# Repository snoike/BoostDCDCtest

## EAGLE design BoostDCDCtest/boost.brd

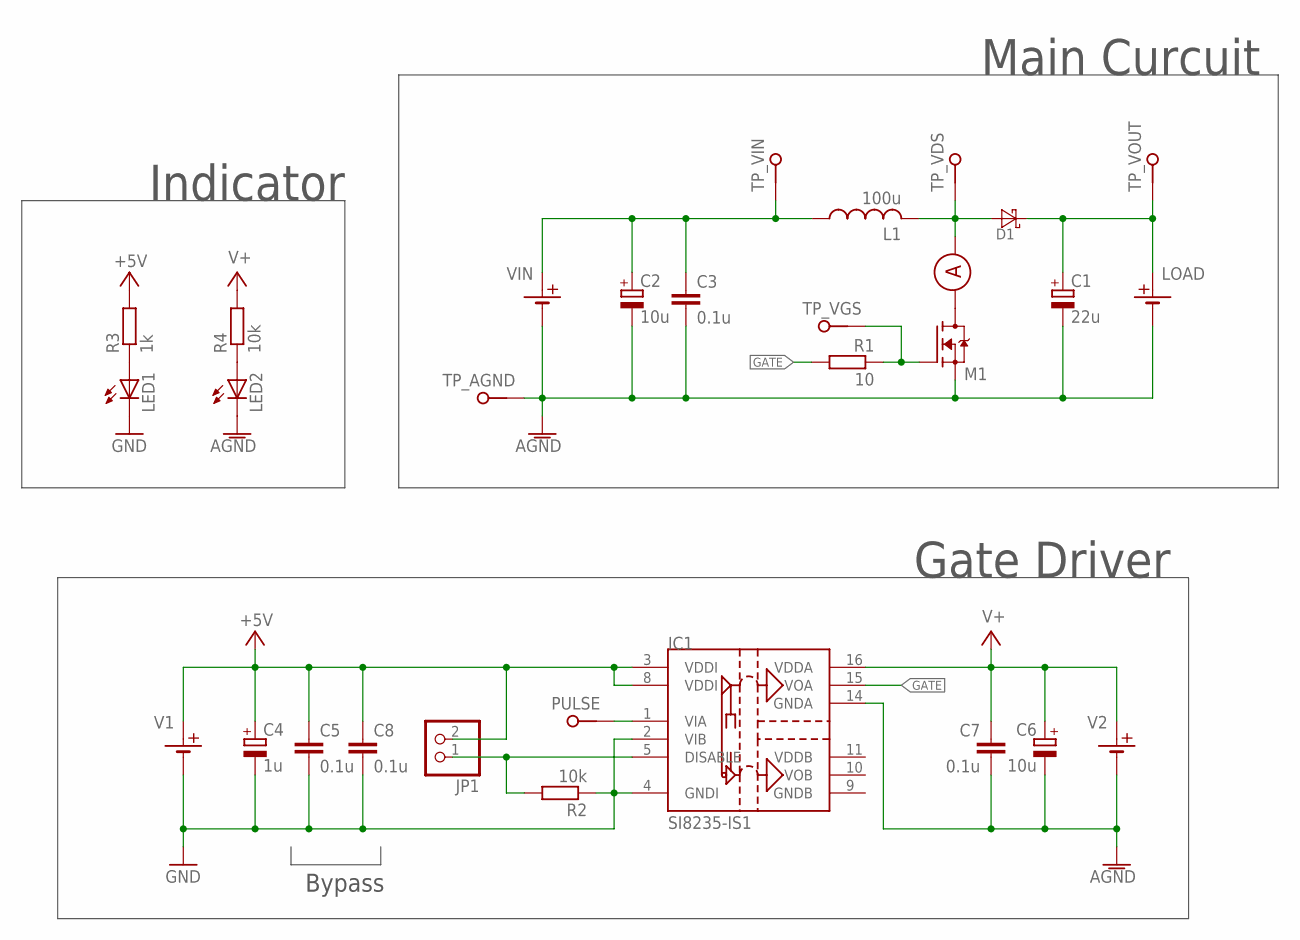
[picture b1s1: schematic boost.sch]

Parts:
C1: 22u; E5-10,5
C2, C6: 10u; E2,5-6
C3, C5, C7, C8: 0.1u; C0805
C4: 1u; E2-5
D1: RB088LAM150TFTR; SOD128
IC1: SI8235-IS1; SO16
JP1: PINHD-1X2; 1X02
L1: 100u; MURATA_19RXXXC
LED1, LED2: LEDCHIPLED_0805; CHIPLED_0805
LOAD: POWER_SUPPLY_L; SOURCE_HIGH
M1: FET_ON_SOCKET; ICTS-TO3P
PULSE: PIN
R1: 10; R2512
R2, R4: 10k; R0805
R3: 1k; R0805
TP_AGND: PIN
TP_VDS: PIN
TP_VGS: PIN
TP_VIN: PIN
TP_VOUT: PIN
U$1: AMMETER
V1, V2: POWER_SUPPLY; 526702AX
VIN: POWER_SUPPLY_L; SOURCE_HIGH

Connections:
+5V: C4.+, C5.1, C8.1, IC1.3 (VDDI), IC1.8 (VDDI), JP1.2, R3.2, V1.P
AGND: C1.-, C2.-, C3.2, C6.-, C7.2, IC1.14 (GNDA), LED2.C, LOAD.N, M1.S0 (S), M1.S1 (S), TP_AGND.1, V2.N, VIN.N
GATE: IC1.15 (VOA), R1.2
GND: C4.-, C5.2, C8.2, IC1.2 (VIB), IC1.4 (GNDI), LED1.C, R2.1, V1.N
GNDB: IC1.9 (GNDB)
unnamed: C2.+, C3.1, L1.1, TP_VIN.1, VIN.P
unnamed: D1.A, L1.2, TP_VDS.1, U$1.P$2
unnamed: M1.G0 (G), M1.G1 (G), R1.1, TP_VGS.1
unnamed: M1.D0 (D), M1.D1 (D), U$1.P$1
unnamed: IC1.5 (DISABLE), JP1.1, R2.2
unnamed: IC1.1 (VIA), PULSE.1
unnamed: C1.+, D1.C, LOAD.P, TP_VOUT.1
unnamed: LED1.A, R3.1
unnamed: LED2.A, R4.1
V+: C6.+, C7.1, IC1.16 (VDDA), R4.2, V2.P
VDDB: IC1.11 (VDDB)

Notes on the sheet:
Main Curcuit
Gate Driver
Indicator
Bypass

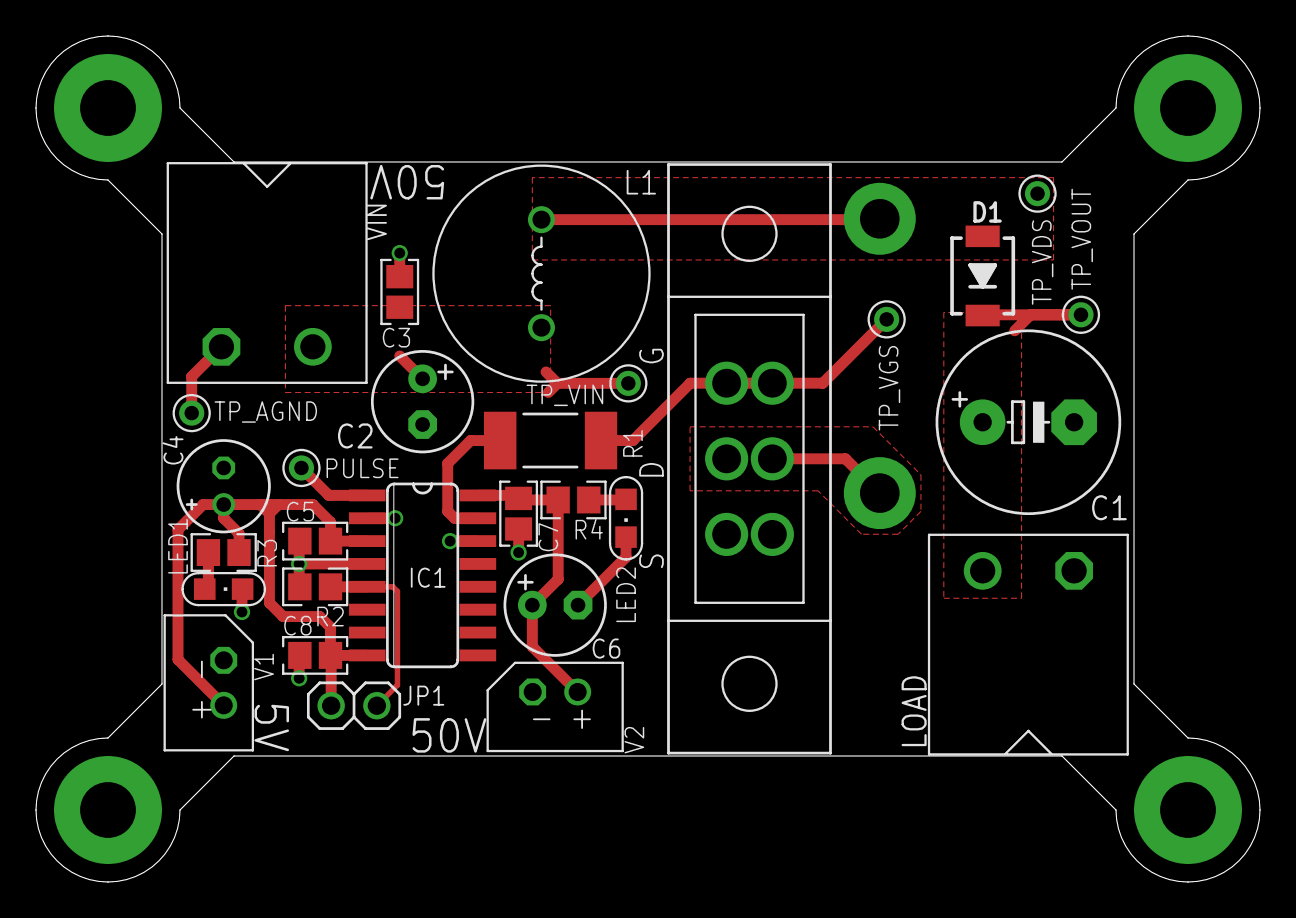
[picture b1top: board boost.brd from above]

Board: 2 copper layers, 68.0 x 47.0 mm, 30 parts (1 on the bottom side), 14 nets.

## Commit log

2020-06-08 1st sch completed
2020-06-08 1st brd completed
    sch has been also editted because there is some issues of tolerance in the test situation.
2020-06-08 add 4 fixing-arms
